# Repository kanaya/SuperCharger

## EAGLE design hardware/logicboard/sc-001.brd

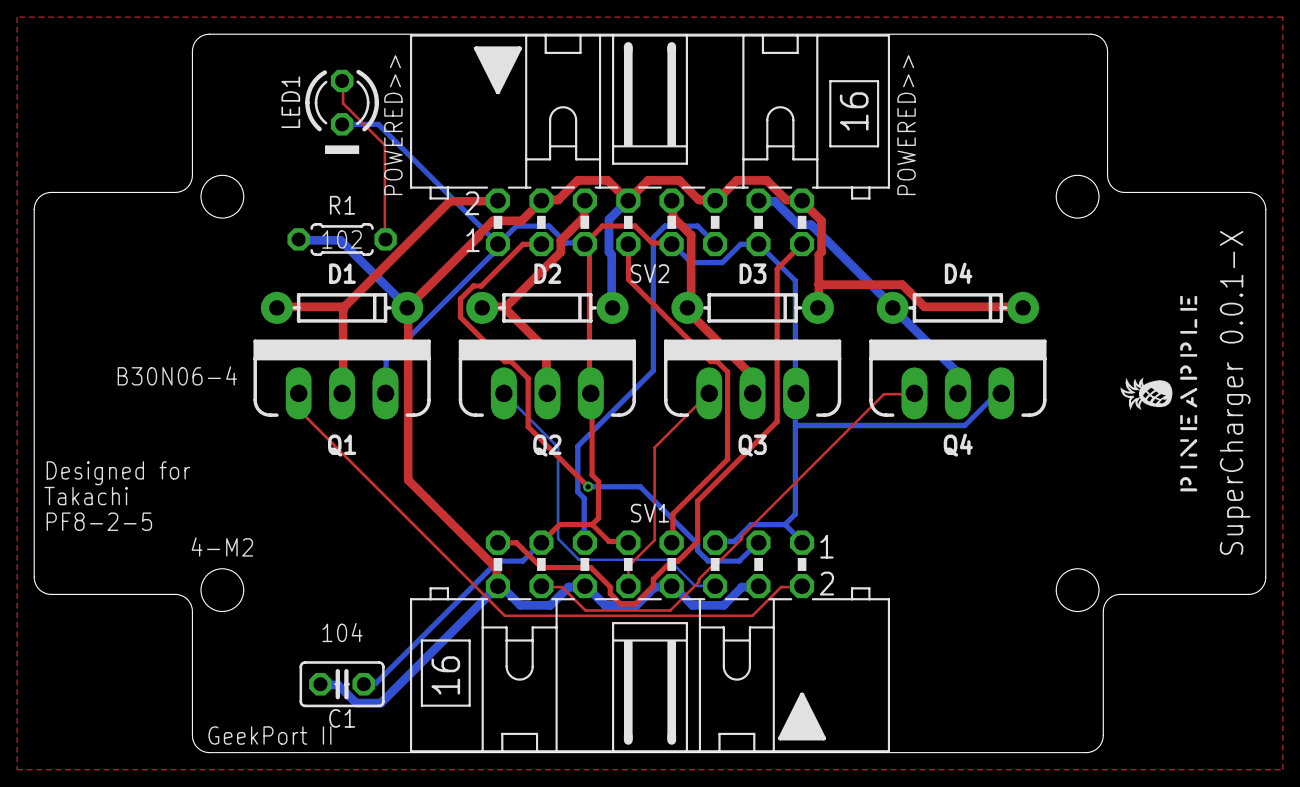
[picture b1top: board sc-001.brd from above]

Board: 2 copper layers, 72.0 x 42.0 mm, 14 parts (0 on the bottom side), 15 nets.

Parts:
C1: C025-025X050
D1, D2, D3, D4: 200mA/100V/1V; DIODE-1N4148
LED1: LED3MM
Q1, Q2, Q3, Q4: 60V/32A/35mΩ; TO220V
R1: 1k; 0204/5
SV1, SV2: ML16L
U$1: PINEAPPLE450_SILK

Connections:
ANLG0: SV1.3, SV2.3
ANLG1: SV1.7, SV2.7
ANLG2: SV1.11, SV2.11
ANLG3: SV1.15, SV2.15
DRVR0: D1.A, Q1.2, SV2.2
DRVR1: D2.A, Q2.2, SV2.6
DRVR2: D3.A, Q3.2, SV2.10
DRVR3: D4.A, Q4.2, SV2.14
DTCT0: Q1.1, SV1.2
DTCT1: Q2.1, SV1.6
DTCT2: Q3.1, SV1.10
DTCT3: Q4.1, SV1.14
GND: C1.2, LED1.K, Q1.3, Q2.3, Q3.3, Q4.3, SV1.1, SV1.5, SV1.9, SV1.13, SV2.1, SV2.5, SV2.9, SV2.13
VCC2LED: LED1.A, R1.2
VCC/2: C1.1, D1.C, D2.C, D3.C, D4.C, R1.1, SV1.4, SV1.8, SV1.12, SV1.16, SV2.4, SV2.8, SV2.12, SV2.16

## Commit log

2022-10-05 Imported from GeekBox.
2022-10-05 Changed board size.
2022-10-05 Added parts.
2022-10-09 Schematic.
2022-10-09 Routed.
2022-10-14 Silk.
2022-11-26 Ext DC port.

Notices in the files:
parts and their libraries:
SparkFun-DiscreteSemi: Licensing: Creative Commons ShareAlike 4.0 International - https://creativecommons.org/licenses/by-sa/4.0
